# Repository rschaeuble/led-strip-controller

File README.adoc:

= LED Strip Controller

An LED strip controller for up to three RGB[W] LED strips, controlled over WiFi + MQTT.

== Current State

* Hardware
** Circuit schematic: nearly complete (for an initial version)
*** A switch mode power supply module needs to be selected.
*** External connectors need to be selected; right now the schematic uses simple pin headers.
** PCB layout: not yet started.
* Software: prototype exists; will be released in the following weeks after some cleanup and polishing. 

== Features

Up to three independently controllable LED strips: ::
+
--
When decorating shelves, TV racks or similar with LED strips, having several
shorter strips glowing in different colors can look nicer than having one longer strip.
However, with usual LED strip controllers, each strip requires its own controller plus power supply. In the end, all those small boxes and their
power bricks don't really look all that pretty.

With this controller, three separate LED strips can be driven with just one small box and its power brick.
--

MQTT interface: ::
+
--
The controller connects (via WiFi) to an MQTT broker, from which it receives
commands and to where it posts its current state.

Right now, the controller supports the following message formats:

* https://www.home-assistant.io/components/light.mqtt_json/[MQTT JSON Light], with support for brightness, RGB colors and white value.

Support for other message formats (e.g. https://www.home-assistant.io/components/light.mqtt/[MQTT Light])
might follow later.

--

== Documentation

* Hardware: link:hardware/led-strip-controller-esp8266/README.adoc[led-strip-controller-esp8266].

== Licenses

=== Software

The software in this repository, with the exception of included third-party works, is licensed under
the link:LICENSE_software.txt[MIT license].

=== Hardware

The hardware designs (schematics, PCB layouts, symbols and footprints etc.) in this repository,
with the exception of included third-party works, are licensed under the
link:http://creativecommons.org/licenses/by-sa/4.0/[Creative Commons Attribution-ShareAlike 4.0 International License].

=== Third-Party Works

Included third-party works (in the directory `3rd-party`) are licensed under their own terms.
Please check the respective licenses.

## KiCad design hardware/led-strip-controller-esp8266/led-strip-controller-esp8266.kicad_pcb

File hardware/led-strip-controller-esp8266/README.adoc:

= ESP8266 based LED Strip Controller
:toc:
:sectnums:
:icons: font

== Hardware Design

Schematic and PCB layout are created using KiCad 5. The project files can be found in the `hardware` directory.

Exports for viewing without KiCad also exist. These should (hopefully) be pretty up-to-date.

.Exports:
* link:exports/led-strip-controller-esp8266.pdf[Schematic]

== Main Components

ESP-WROOM-02::
+
--
Microcontroller with built-in WiFi.
--

PCA9685::
+
--
PWM LED controller with 16 channels and I^2^C bus interface.

As the ESP8266 does not have enough pins to drive 12 LED channels (3 * RGBW), a dedicated chip has to do this work.
--

== Power Supply

The circuit consists of two power nets: a 12{nbsp}V net for the LED strips and a 3.3{nbsp}V net for everything else.

The 12{nbsp}V are provided by an external power supply. The LED strips are directly connected to this power rail.

The 3.3{nbsp}V are provided by an on-circuit power regulator whose input is connected to the 12{nbsp}V rail.
With a voltage difference of about 9{nbsp}V and up to 500{nbsp}mA current draw by the ESP8266 alone,
a linear regulator is too inefficient, so a switching mode regulator is used.

.Current draw of individual components:
* ESP-WROOM-02: 500{nbsp}mA
* PCA9685: 10{nbsp}mA (just the chip, without any driven LEDs)
* One or two status LEDs: 40{nbsp}mA

Adding some buffer, an 800{nbsp}mA power supply should suffice easily.

== Design Consideration

This section is a collection of various design considerations.

=== Switch Mode Power Supply: build your own or buy (OPEN)

As this is my first real hardware project and given my complete lack of experience with switch mode power supplies,
I ruled out building my own regulator circuit (e.g. based on LM2595 or LM2675).
Instead, an all-in-one regulator module will be used.

.Module Candidates
[%header,cols="2,1,1a,1,3a"]
|===
|Name +
(Manufacturer)
|Datasheet
|Distributor 
|Price
|Notes

|VXO7803-1000 +
(CUI)
|https://www.cui.com/product/resource/digikeypdf/vxo78-1000.pdf[Datasheet]
|https://www.digikey.de/product-detail/de/cui-inc/VXO7803-1000/102-4257-ND/7350296[Digi-Key],
https://www.mouser.de/ProductDetail/CUI/VXO7803-1000?qs=sGAEpiMZZMsc0tfZmXiUnQ%252bwKZhbvwnu%252bcROBF%2f6Q16XdELjoC0Jhg%3d%3d[Mouser]
|2.22-2.35{nbsp}€
|

|VX7803-1000 +
(CUI)
|https://www.cui.com/product/resource/digikeypdf/vx78-1000.pdf[Datasheet]
|https://www.digikey.de/product-detail/de/cui-inc/VX7803-1000/102-4252-ND/7350291[Digi-Key]
|2,80{nbsp}€
|

|R-78E3.3-1.0 +
(Recom Power)
|https://www.recom-power.com/pdf/Innoline/R-78Exx-1.0.pdf[Datasheet]
|https://www.digikey.de/product-detail/de/recom-power/R-78E3.3-1.0/945-2409-5-ND/5327711[Digi-Key],
https://www.mouser.de/ProductDetail/RECOM-Power/R-78E33-10?qs=sGAEpiMZZMsc0tfZmXiUnbaEjpYStdRIFUgifFXFkklVvzJFhjySMg%3d%3d[Mouser]
|2,67-2,80{nbsp}€
|

|MEZD71201A-F +
(Monolithic Power Systems)
|http://www.monolithicpower.com/pub/media/document/mEZD71201Ar1.5.pdf[Datasheet]
|https://www.digikey.de/product-detail/de/monolithic-power-systems-inc/MEZD71201A-F/1589-1457-ND/6823820[Digi-Key],
https://www.mouser.de/ProductDetail/Monolithic-Power-Systems-MPS/mEZD71201A-F?qs=sGAEpiMZZMsc0tfZmXiUnQ%252bwKZhbvwnunWq9oxKi2Cb1IKU3wZf98Q%3d%3d[Mouser]
|2,76-2,90{nbsp}€
|

|TR10S3V3 +
(XP Power)
|https://www.xppower.com/Portals/0/pdfs/SF_TR10.pdf[Datasheet]
|https://www.digikey.de/product-detail/de/xp-power/TR10S3V3/1470-3970-ND/6707494[Digi-Key]
|3,40{nbsp}€
|

|===

Product search:

* https://www.digikey.de/products/de/power-supplies-board-mount/dc-dc-converters/922?k=&pkeyword=&FV=8f40064%2C8f40013%2C8f40014%2C8f40016%2C8f40018%2C8f40019%2C8f4001a%2C8f40022%2C8f40032%2C8f40034%2C8f40042%2C8f40043%2C8f40044%2C8f4005b%2C11800075%2C1180007d%2C11800086%2C11800541%2C11800542%2C11800543%2C1180008b%2C11800580%2C11800581%2C11800582%2C11800583%2C1180058a%2C1180058c%2C1180058d%2C118005bd%2C118000a5%2C11800679%2C11800681%2C11800687%2C118006a5%2C118006a7%2C118000b1%2C118000b3%2C118000b5%2C118000b7%2C118000bc%2C118000cb%2C118000cf%2C118000d0%2C118000d1%2C118000d4%2C118000db%2C11800018%2C118000f4%2C118000fd%2C118009e8%2C118009ea%2C118000ff%2C11800101%2C11800108%2C1180010a%2C11800a6a%2C11800aa7%2C11800aa8%2C11800aa9%2C11800112%2C11800118%2C1180011d%2C11800125%2C1180012d%2C11800145%2C11800151%2C11800156%2C11800157%2C1180015b%2C1180016e%2C1180017e%2C11800182%2C11800187%2C11800188%2C11800192%2C118001a9%2C118001aa%2C1180002b%2C118001b0%2C118001b1%2C118001ec%2C118001f4%2C118001f9%2C11800212%2C11800228%2C1180022a%2C1180023a%2C1180023c%2C1180023d%2C1180023e%2C1180003a%2C1180025c%2C1180003d%2C118002b3%2C1180004a%2C1180004f%2C1180005f%2C16fc000b%2C16fc000c%2C16fc0085%2C16fc0091%2C16fc0002%2C16fc0014%2C16fc00d8%2C16fc010a%2C16fc0115%2C16fc0116%2C16fc001c%2C16fc001f%2C16fc0020%2C16fc0022%2C16fc0027%2C16fc002f%2C16fc0031%2C16fc0008%2C16fc0055%2C16fc0009%2C17d4005e%2C1f140000%2Cii1%7C2211%2Cffe0039a&quantity=0&ColumnSort=1000011&page=1&nstock=1&pageSize=25[Digi-Key]
* https://www.mouser.de/Power/DC-DC-Converters/_/N-brvxe?P=1yx5k7vZ1yxt7f5&Rl=brvxeZgjdhnxZ1yxt78pZ1yxt74iSGT&Ns=Pricing|0[Mouser] 

=== Overload Protection for LED strips (OPEN)

If the LED strips connected to the controller draw more power than the power supply and/or the circuitry
can handle, this could potentially cause damage.

To prevent this, some kind of current limiter could be added to the circuitry feeding the LED strips.

.Open questions:
* How would the overcurrent protection work? Autonomous hardware, or with support from the firmware?
* How about a current meter (with a I^2^C interface) that the firmware could read out? The current power draw
  could be reported via MQTT, providing for a nice little feature.

=== ESD Protection

The following connections are accessible when the controller is inside a closed enclosure:

* LED strip connectors.
* Power supply jack.
* Programming lines:
** RX/TX
** GND
** Reset
** Firmware flashing mode selector

While ESD protection for a simple and cheap product as this is probably a bit overkill,
adding it would teach me something new, so I'll likely do it.

To do:

* Learn about different ESD protection techniques
** Diodes to V+, one to V-.
** Diodes only to V-.
* Extend schematic.

.Reading List
* http://www.onsemi.com/pub/Collateral/TND335-D.PDF
* https://www.onsemi.com/pub/Collateral/AND8231-D.PDF

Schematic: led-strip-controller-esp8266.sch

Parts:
C1, C3, C4: 0.1uF; C_0805_2012Metric_Pad1.29x1.40mm_HandSolder
C2: 10uF; C_0805_2012Metric_Pad1.29x1.40mm_HandSolder
D1: TVS3V3L4U; TSOP-6_1.65x3.05mm_P0.95mm
D2: LED; LED_0805_2012Metric
J2: Conn_01x05_Female; PinHeader_1x05_P1.00mm_Vertical
J3: Barrel_Jack; BarrelJack_Horizontal
R1, R2, R3, R4: 10k; R_0805_2012Metric_Pad1.29x1.40mm_HandSolder
R5: 470; R_0805_2012Metric_Pad1.29x1.40mm_HandSolder
TP1: Test_Point; Pin_D1.0mm_L10.0mm
U1: ESP-13-WROOM-02
U2: PCA9685PW; TSSOP-28_4.4x9.7mm_P0.65mm
U3: R-78HB3.3-0.5; Converter_DCDC_RECOM_R-78HB-0.5_THT

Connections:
+3V3: C2.2, C3.2, C4.1, R1.2, R2.2, R4.1, U1.1, U2.28, U3.3 (OUT)
+12V: J3.1, U3.1 (IN); also elsewhere on the board
/BOOT: D1.6, J2.3, U1.8
/LED_PWM1: U2.9, U2.11, U2.13, U2.16, U2.18, U2.20; also elsewhere on the board
/LED_PWM2: U2.10; also elsewhere on the board
/LED_PWM4: U2.12; also elsewhere on the board
/LED_PWM6: U2.15; also elsewhere on the board
/LED_PWM8: U2.17; also elsewhere on the board
/LED_PWM10: U2.19; also elsewhere on the board
/LED_PWM12: U2.21; also elsewhere on the board
/RESET: D1.4, J2.2, U1.15
/RX: D1.1, J2.5, U1.11
/SCL: R2.1, U1.5, U2.26
/SDA: R1.1, U1.4, U2.27
/TRIGGER: TP1.1, U2.22
/TX: D1.3, J2.4, U1.12
unnamed: C1.1, R4.2, U1.2
unnamed: D2.2, R5.1
unnamed: R3.1, U1.6
unnamed: R5.2, U1.10

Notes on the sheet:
I2C Bus
NOTE: needs to be replaced with a pin-compatible model with high enough output current.
External connectors
Power Supply

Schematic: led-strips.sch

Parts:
J1: Conn_01x15_Female; PinHeader_1x15_P1.00mm_Vertical
Q1, Q2, Q3, Q4, Q5, Q6: DMN3018SSD; SOIC-8_3.9x4.9mm_P1.27mm

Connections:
+12V: J1.5, J1.10, J1.15; also elsewhere on the board
/LED Strips/LED1: J1.14, Q1.7 (D1), Q1.8 (D1)
/LED Strips/LED2: J1.13, Q1.5 (D2), Q1.6 (D2)
/LED Strips/LED3: J1.12, Q2.7 (D1), Q2.8 (D1)
/LED Strips/LED4: J1.11, Q2.5 (D2), Q2.6 (D2)
/LED Strips/LED5: J1.9, Q3.7 (D1), Q3.8 (D1)
/LED Strips/LED6: J1.8, Q3.5 (D2), Q3.6 (D2)
/LED Strips/LED7: J1.7, Q4.7 (D1), Q4.8 (D1)
/LED Strips/LED8: J1.6, Q4.5 (D2), Q4.6 (D2)
/LED Strips/LED9: J1.4, Q5.7 (D1), Q5.8 (D1)
/LED Strips/LED10: J1.3, Q5.5 (D2), Q5.6 (D2)
/LED Strips/LED11: J1.2, Q6.7 (D1), Q6.8 (D1)
/LED Strips/LED12: J1.1, Q6.5 (D2), Q6.6 (D2)
/LED_PWM1: Q1.2 (G1), Q2.2 (G1), Q3.2 (G1), Q4.2 (G1), Q5.2 (G1), Q6.2 (G1); also elsewhere on the board
/LED_PWM2: Q1.4 (G2); also elsewhere on the board
/LED_PWM4: Q2.4 (G2); also elsewhere on the board
/LED_PWM6: Q3.4 (G2); also elsewhere on the board
/LED_PWM8: Q4.4 (G2); also elsewhere on the board
/LED_PWM10: Q5.4 (G2); also elsewhere on the board
/LED_PWM12: Q6.4 (G2); also elsewhere on the board

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
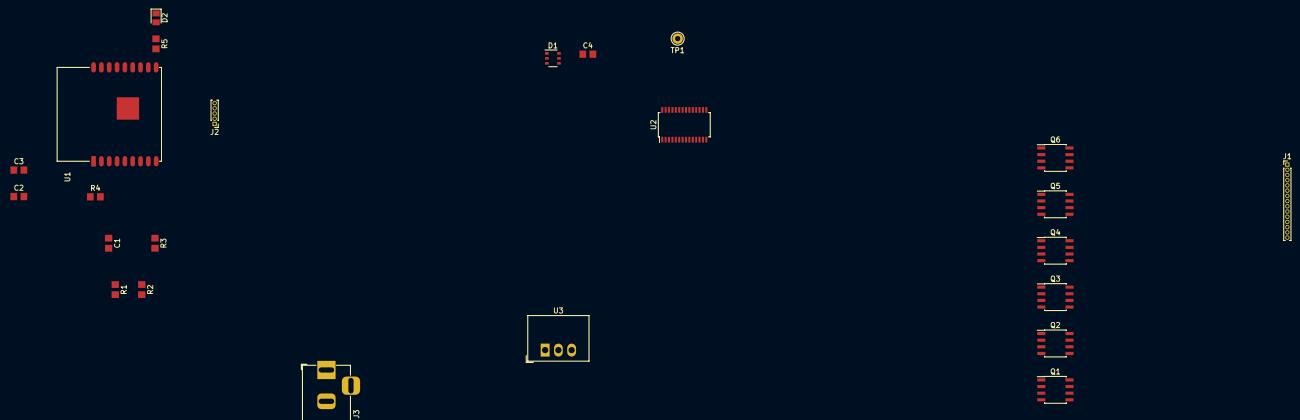
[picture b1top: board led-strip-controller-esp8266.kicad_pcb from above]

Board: 2 copper layers, 24 parts (0 on the bottom side), 33 nets, no tracks yet.

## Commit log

2018-05-29 Initial commit, just with a README.
2018-05-29 Add information about 3rd-party dependencies.
2018-05-29 Squashed '3rd-party/kicad-libs/kicad-ESP8266/' content from commit ab37bad
    git-subtree-dir: 3rd-party/kicad-libs/kicad-ESP8266
    git-subtree-split: ab37bad0510ac6d2f79f07f9f6303ad56de5b2df
2018-05-29 Add initial (quite empty) KiCad project.
2018-05-29 Begin with schematic drawing.
2018-06-02 Add documentation and license terms.
2018-06-02 Add "features" section to README.
2018-06-02 Document current state in README.
2018-06-02 Remove a section from the hardware documentation, because it wasn't really all that useful.
2018-06-02 Fix typos in documentation.
2018-06-02 More work on the schematic.
2018-06-02 Beautify link in documentation.
2018-06-02 Make table more readable.
2018-06-03 Remove file that's not used any more.
2018-06-03 Add power supply module and power jack.
2018-06-03 Update "current state" section in README.
2018-06-03 Add PDF export of the schematic.
2018-06-03 KiCad project file update.
2018-06-03 Add decoupling capacitor to power supply pin of PCA9685.
2018-06-03 Add 3.3V rail to external programming interface, and update schematic PDF.
2018-06-21 Create a symbol library for my own symbols.
2018-06-21 Add symbol for Diodes Inc. DMN3018SSD.
2018-06-21 Add TVS3V3L4U TVS diode.
2018-06-21 Add TVS diode and new MOSFET array to schematic.
2018-07-01 Add status LED and resistor.
2018-07-01 Add a mode/reset button.
2018-07-01 Updated schematics PDF.
